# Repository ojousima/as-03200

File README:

This repository serves files of an Aalto university project.
It is meant for internal use of our team, but feel free to poke around.

We're happy to address any questions and comments.

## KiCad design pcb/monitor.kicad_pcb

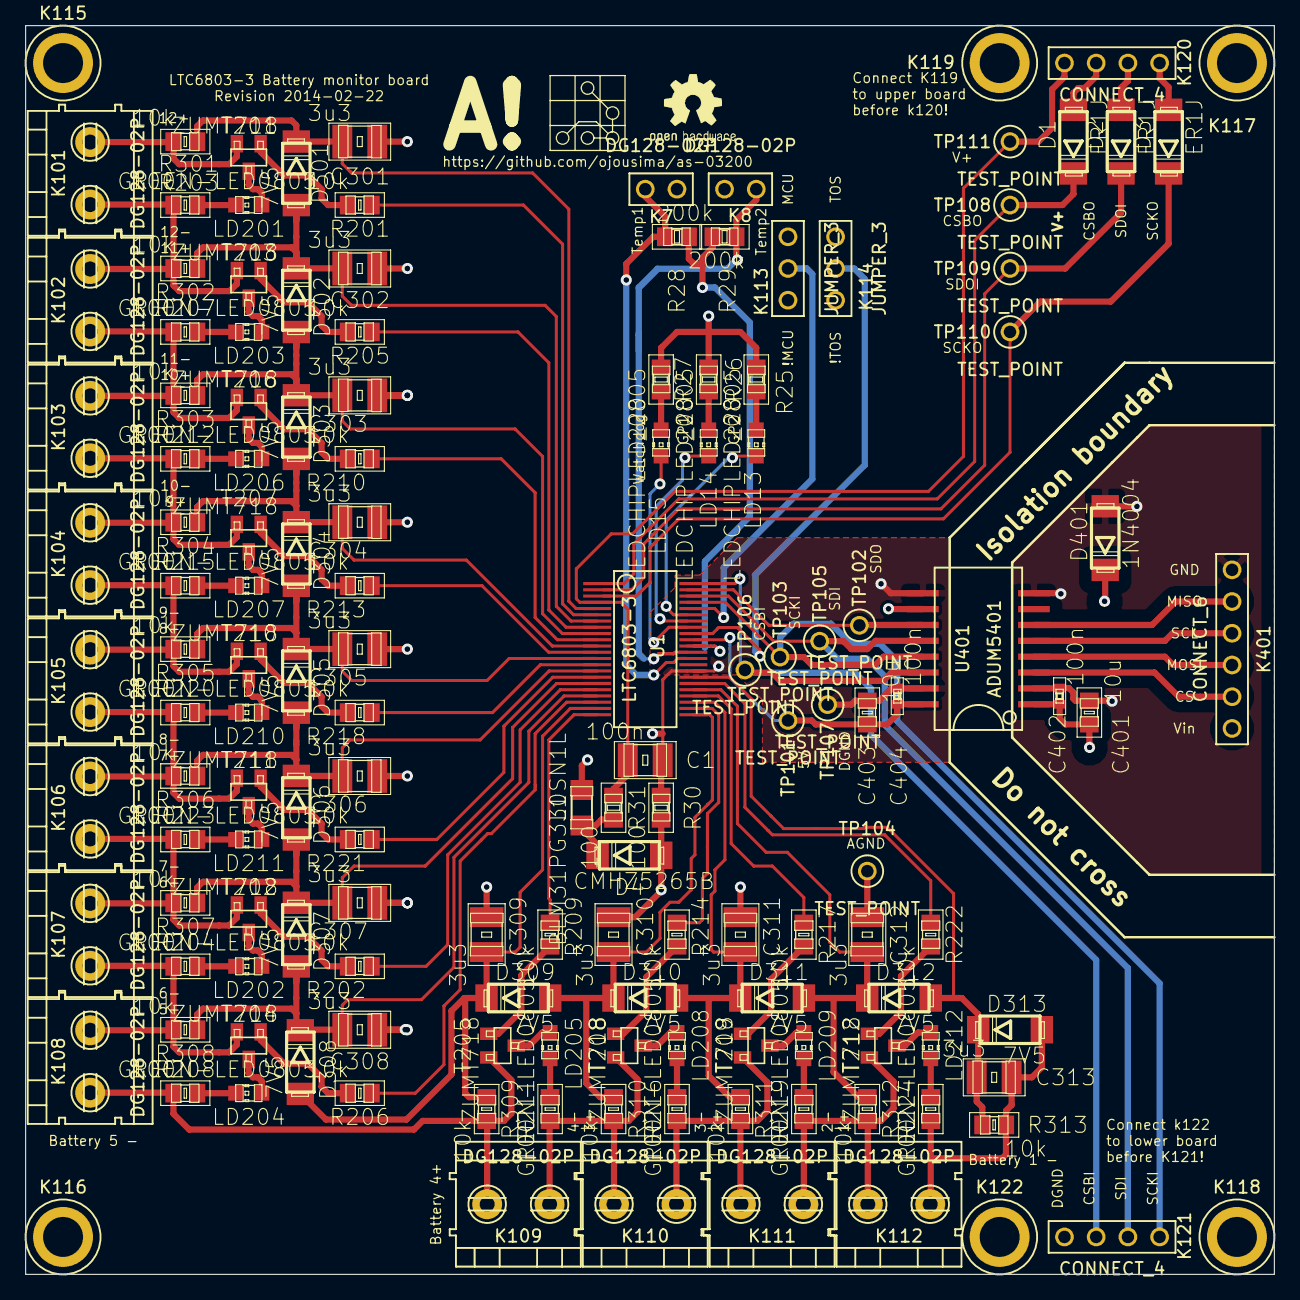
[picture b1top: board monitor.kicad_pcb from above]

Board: 4 copper layers, 100.0 x 100.0 mm, 146 parts (0 on the bottom side), 105 nets.

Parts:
C1: 100n; rcl-C1210
C301, C302, C303, C304, C305, C306, C307, C308, C309, C310, C311, C312, C313: 3u3; rcl-C1210
C401, C403: 10u; rcl-C0805
C402, C404: 100n; rcl-C0402
D1, D2, D3: ER1J; diode-1-DO214AA
D4: CMHZ5265B; diode-1-DO214AA
D301, D302, D303, D304, D305, D306, D307, D308, D309, D310, D311, D312, D313: 7V5; diode-1-DO214AA
D401: 1N4004; diode-1-DO214AA
K7, K8: DG128-02P; CONNECT_2_2mm54_VERT
K101, K102, K103, K104, K105, K106, K107, K108, K109, K110, K111, K112: DG128-02P; CONNECT_2_5.00mm_SCREW_DG128-02P_DG128-5.0-02P-14-00A(H)
K113, K114: JUMPER_3; JUMPER_3_2.54mm
K115, K116, K117, K118, K119, K122: MOUNT; M3_MOUNT_BARE
K120, K121: CONNECT_4; 2_54_MM_HEADER_4
K401: CONNECT_6; 2_54_MM_HEADER_6
L1: BLM31PG330SN1L; rcl-L1206
LD13, LD14, LD15: LEDCHIPLED_0805; led-CHIP-LED0805
LD201, LD202, LD203, LD204, LD205, LD206, LD207, LD208, LD209, LD210, LD211, LD212: GREEN-LED0805; led-CHIP-LED0805
R25, R26, R27: 220; rcl-R0805
R28, R29: 200k; rcl-R0805
R30, R31: 100; rcl-R0805
R201, R202, R205, R206, R209, R210, R213, R214, R217, R218, R221, R222, R301, R302, R303, R304, R305, R306, R307, R308, R309, R310, R311, R312, R313: 10k; rcl-C0805
R203, R204, R207, R208, R211, R212, R215, R216, R219, R220, R223, R224: 100; rcl-C0805
T201, T202, T203, T204, T205, T206, T207, T208, T209, T210, T211, T212: ZUMT718; transistor-SOT23-BEC
TP101, TP102, TP103, TP104, TP105, TP106, TP107, TP108, TP109, TP110, TP111: TEST_POINT; Keystone_Electronics_5000
U1: LTC6803-3; SSOP44_HS
U401: ADUM5401; SOIC_16_WIDE

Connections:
/CSBO: D1.C, TP108.1, U1.1
/GPIO1: LD14.C, U1.38
/GPIO2: LD13.C, U1.39
/Isolation/5V: C403.1, C404.1, K113.3, K114.3, R25.1, R26.1, R27.1, TP101.1, U1.35, U401.10, U401.16
/Isolation/CS: K401.5, U401.3
/Isolation/CSBI: K121.2, TP106.1, U1.44, U401.14
/Isolation/GND1: C401.2, C402.2, D401.A, K401.1, U401.2, U401.8
/Isolation/MISO: K401.2, U401.6
/Isolation/MOSI: K401.4, U401.4
/Isolation/SCKI: K121.4, TP103.1, U1.41, U401.13
/Isolation/SCL: K401.3, U401.5
/Isolation/SDI: K121.3, TP105.1, U1.42, U401.12
/Isolation/SDO: TP102.1, U1.43, U401.11
/Isolation/Vin: C401.1, C402.1, D401.C, K401.6, U401.1
/Lowpass/BATT1+: K111.2, K112.1, R219.2, R312.2, T212.E
/Lowpass/BATT2+: K110.2, K111.1, R216.2, R311.2, T209.E
/Lowpass/BATT3+: K109.2, K110.1, R211.2, R310.2, T208.E
/Lowpass/BATT4+: K108.2, K109.1, R208.2, R309.2, T205.E
/Lowpass/BATT5+: K107.2, K108.1, R204.2, R308.2, T204.E
/Lowpass/BATT6+: K106.2, K107.1, R223.2, R307.2, T202.E
/Lowpass/BATT7+: K105.2, K106.1, R220.2, R306.2, T211.E
/Lowpass/BATT8+: K104.2, K105.1, R215.2, R305.2, T210.E
/Lowpass/BATT9+: K103.2, K104.1, R212.2, R304.2, T207.E
/Lowpass/BATT10+: K102.2, K103.1, R207.2, R303.2, T206.E
/Lowpass/BATT11+: K101.2, K102.1, R203.2, R302.2, T203.E
/Lowpass/C0: C313.2, D312.A, D313.C, R313.1, U1.29
/Lowpass/C1: C312.2, D311.A, D312.C, R312.1, U1.27
/Lowpass/C2: C311.2, D310.A, D311.C, R311.1, U1.25
/Lowpass/C3: C310.2, D309.A, D310.C, R310.1, U1.23
/Lowpass/C4: C309.2, D308.A, D309.C, R309.1, U1.21
/Lowpass/C5: C308.2, D307.A, D308.C, R308.1, U1.19
/Lowpass/C6: C307.2, D306.A, D307.C, R307.1, U1.17
/Lowpass/C7: C306.2, D305.A, D306.C, R306.1, U1.15
/Lowpass/C8: C305.2, D304.A, D305.C, R305.1, U1.13
/Lowpass/C9: C304.2, D303.A, D304.C, R304.1, U1.11
/Lowpass/C10: C303.2, D302.A, D303.C, R303.1, U1.9
/Lowpass/C11: C302.2, D301.A, D302.C, R302.1, U1.7
/Lowpass/C12: C301.2, D301.C, R301.1, U1.5
/SCKO: D3.C, TP110.1, U1.3
/SDOI: D2.C, TP109.1, U1.2
/TOS: K114.2, U1.36
/V+: C1.2, K120.1, R31.1, TP111.1, U1.4
/VMODE: K113.2, U1.40
/Vref: R28.2, R29.2, U1.34
/Vtemp1: K7.2, R28.1, U1.32
/Vtemp2: K8.1, R29.1, U1.33
/WDTB: LD15.C, U1.37
/discharge/BATT12+: K101.1, K119.1, L1.1, R301.2, T201.E
/discharge/S1: R222.1, U1.28
/discharge/S2: R217.1, U1.26
/discharge/S3: R214.1, U1.24
/discharge/S4: R209.1, U1.22
/discharge/S5: R206.1, U1.20
/discharge/S6: R202.1, U1.18
/discharge/S7: R221.1, U1.16
/discharge/S8: R218.1, U1.14
/discharge/S9: R213.1, U1.12
/discharge/S10: R210.1, U1.10
/discharge/S11: R205.1, U1.8
/discharge/S12: R201.1, U1.6
AGND: C301.1, C302.1, C303.1, C304.1, C305.1, C306.1, C307.1, C308.1, C309.1, C310.1, C311.1, C312.1, C313.1, D4.A, D313.A, K112.2, K122.1, R30.2, R224.2, R313.2, TP104.1
DGND: C1.1, C403.2, C404.2, K7.1, K8.2, K113.1, K114.1, K121.1, R30.1, TP107.1, U1.30, U401.9, U401.15
unnamed: D1.A, K120.2
unnamed: D2.A, K120.3
unnamed: D3.A, K120.4
unnamed: D4.C, L1.2, R31.2
unnamed: LD13.A, R25.2
unnamed: LD14.A, R26.2
unnamed: LD15.A, R27.2
unnamed: LD201.A, T201.C
unnamed: LD201.C, R203.1
unnamed: LD202.A, T202.C
unnamed: LD202.C, R204.1
unnamed: LD203.A, T203.C
unnamed: LD203.C, R207.1
unnamed: LD204.A, T204.C
unnamed: LD204.C, R208.1
unnamed: LD205.A, T205.C
unnamed: LD205.C, R211.1
unnamed: LD206.A, T206.C
unnamed: LD206.C, R212.1
unnamed: LD207.A, T207.C
unnamed: LD207.C, R215.1
unnamed: LD208.A, T208.C
unnamed: LD208.C, R216.1
unnamed: LD209.A, T209.C
unnamed: LD209.C, R219.1
unnamed: LD210.A, T210.C
unnamed: LD210.C, R220.1
unnamed: LD211.A, T211.C
unnamed: LD211.C, R223.1
unnamed: LD212.A, T212.C
unnamed: LD212.C, R224.1
unnamed: R201.2, T201.B
unnamed: R202.2, T202.B
unnamed: R205.2, T203.B
unnamed: R206.2, T204.B
unnamed: R209.2, T205.B
unnamed: R210.2, T206.B
unnamed: R213.2, T207.B
unnamed: R214.2, T208.B
unnamed: R217.2, T209.B
unnamed: R218.2, T210.B
unnamed: R221.2, T211.B
unnamed: R222.2, T212.B

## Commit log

2014-01-26 Barebones of the project
2014-01-29 Updated files for newer version of kicad
2014-01-29 Added stub document for design guidelines
2014-01-30 Added serial ports to schema
2014-01-30 Added few footprints, matched components for footprints
2014-01-30 unified naming of components
2014-01-30 Switched a few pins, added NC pin
2014-01-30 Changed connectors to screw terminals
2014-01-30 Clarified drawings
2014-01-30 Switched a few nets for routing
2014-01-30 Enlargened board
2014-01-31 Added documentation for monitor PCB
2014-01-31 Updated simulations
2014-01-31 Added raw simulation data to gitignore
2014-01-31 Matched schematic with design document
2014-01-31 Matched pcb with schematic
2014-01-31 added licence information of external libraries
2014-02-02 Add missing connections to schema
2014-02-02 Switch ground connection
2014-02-02 Change to 4 layer design
2014-02-02 Add temperature + led connections
2014-02-05 Add PSU bypassing
2014-02-05 Move LPF and discharge to subcircuits
2014-02-05 Add isolation to MCU comms
2014-02-07 Add doc of isolation
2014-02-07 Add isolation to schema
2014-02-07 Update annotation, add symbol for ADuM5401
2014-02-08 Add symbol and footprint for test point
2014-02-08 Add testpoints to schema
2014-02-08 Add orientation mark to SOIC_16_W
2014-02-08 Place grounds to PCB
2014-02-09 Named temp sensor connectors
2014-02-09 Remove groundplanes
2014-02-09 Fix missing junction
2014-02-09 Battery connections
2014-02-09 More connections
2014-02-09 Add temperature connections
2014-02-09 Add jumper documentation
2014-02-09 Fixed few missing junctions in schematic
2014-02-09 First DRC-ok draft
2014-02-15 Add pinheaders, mounting hole
2014-02-15 Change some connectors to 2.54 mm
2014-02-15 Implement changes
2014-02-17 Add LTC6803-1
2014-02-22 Finishing touches
2014-02-22 Add logos
2014-04-03 MC: First implementation: Debug data from Monitor
    Microcontroller can read diagnostics data from monitor card over SPI bus
2014-04-29 SPI code commenting
2014-05-01 Fixed PEC calculation bug.
2014-05-02 Added read/write configuration register functions.
    Functions non-working, need debugging. Only frame for future.
2014-05-03 SW: Fixed functions reading/modifying monitor registers
    - Added functions modifying configuration register
    - Improved debugging messages
2014-05-04 SW: Add function to set monitor comparator duty cycle
2014-05-04 SW: Function name changes. Main loop update.
2014-05-04 SW: Add function to send commands to monitor.
2014-05-04 SW: Add command definitions and monitor self test.
2014-05-04 SW: Debug message.
2014-05-04 SW: Added printWord debug function
2014-05-04 SW: Fixed SPI_readAllVoltages()
    - 12-bit voltage values stored properly in 16-bit variables.
2014-05-04 SW: Improved reading monitor diagnostics register data.
2014-05-04 SW: Removed SPI general receive buffer. Obsolete.
2014-05-04 SW: Added option for user input
    - Function handleInput() added
2014-05-04 SW: Init LED sequence and handle user input to main.
2014-05-04 SW: Added local conf register. Removed debug prints.
    - Separated local and monitor conf register.
    --- Monitor register can be polled every cycle/loop.
    - Remove a lot of obsolete debugging prints.
    - Added print register functions for debugging.
2014-05-04 SW: Monitor status polling done every loop.
2014-05-04 SW: User can specifically print debug data.
2014-05-05 SW: Changed voltage unsigned -> signed.
2014-05-05 SW: Bug fix. Improved debug messages.
    - Fixed bug in setting comparator duty cycle.
    - Improved debug when sending commands to microcontroller.
2014-05-05 SW: Added printing usage instructions.
2014-05-05 SW: Moved monitor definitions.
2014-05-05 SW: Initial balancing logic. Only basic structure.
2014-05-05 SW: Style fix to debug printing.
2014-05-05 match documentation with 1st proto
2014-05-05 Match components with footprint
2014-05-05 First production version
2014-05-06 SW: Updated OV and UV definitions.
2014-05-06 SW: When monitor active command sent on every cycle.
2014-05-06 SW: Moved location of monitor logic.
2014-05-06 SW: Add discharge support for Battery Cells 0-3
2014-05-06 SW: Added function for discharging cell 0.
2014-05-06 SW: Added variables and definitions.
2014-05-06 SW: Improved debug/usage messages.
2014-05-06 SW: Start diagnostics cmd run on every main cycle.
2014-05-07 SW: Toggle adc conversion. Improved usage instructions.
2014-05-07 SW: Bugfix: Error messages won't flood serial output.
2014-05-11 SW: Added support for up to 12 cells. Split functions.
    - 12 cells can be discharged
    - Functions printing debug messages split into separate instances.
2014-05-22 SW: loop_ctr reset to 1, not 0.
2014-05-22 SW: Fixed arduino crash problem/bug.
    - Added F() wrapper to Serial.print calls.
2014-05-22 Fix mistakes found in first prototype
2014-05-22 Update doc to match first prototype
2014-05-22 Add sections references and results.
2014-05-23 Doc: Added final documentation document
    - Contains proposal for final documentation document structure.
2014-05-24 Doc: Updated the software part in final documentation.
2014-05-24 SW: Renamed source file
2014-05-24 More documentation
2014-05-24 Doc: Updated time usage table to final doc. Other minor changes.
2014-05-24 Doc: Add initial design and license
2014-05-24 Add zeners and bypass to simulation
2014-05-24 Fix signal labels
2014-05-24 Reset to origin
2014-05-24 Add references
2014-05-24 Doc: Add hw communication, battery interface and power supply
2014-05-25 Doc: Added text to final doc - software design
2014-05-25 Doc: final doc - Updated Table of Contents. Added references.
2014-05-25 Doc: Added Software outcome to final doc
2014-05-25 Doc: Final doc typo fixes
2014-05-25 Doc: Final doc style fixes
2014-05-25 Doc: Added software features section to final doc
2014-05-25 Doc: Added more time usage stats. Fixed typos etc.
2014-05-25 Doc: Final doc final version. Added pictures
2014-05-25 Doc: Added pdf of final documentation
2014-05-25 Doc: Fixed cross references.
2014-05-25 SW: Moved debug prints to separate file
2014-05-25 SW: Improved help/instructions message
2014-05-25 SW: Removed loop_ctr in main
2014-05-25 SW: Simplified usage of handleInput
2014-05-25 Doc: Added time usage spreadsheet
